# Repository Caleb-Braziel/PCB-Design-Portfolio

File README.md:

# PCB Design Portfolio

This repository contains a curated set of PCB design projects developed for instructional use and technical mentorship. The designs demonstrate practical workflows in schematic capture, hierarchical design, PCB layout, and manufacturability using KiCad and EAGLE.

While many of these projects were created for teaching purposes, they reflect real-world PCB design practices and increasing levels of technical complexity.

---

## Project Overview

The projects in this repository span a range of complexity, from introductory designs to advanced power and embedded systems.

### EAGLE Projects
- **Night Light PCB**  
  A fully fabricated PCB for a night light circuit, including LED and basic power components, laid out and soldered.

### KiCad Projects
- **AC to DC Converter**  
  An AC-DC power supply PCB circuit, designed for voltage conversion and basic power regulation.

- **DC Motor Speed Controller**  
  A PCB for controlling the speed of a DC motor, using discrete components and control circuitry.

- **GPS Tracker with STM32**  
  A microcontroller-based PCB integrating a GPS module for location tracking.

---

## Design Focus

Across these projects, the primary design goals include:
- Clear schematic organization and hierarchy
- Manufacturable PCB layouts
- Proper grounding and power distribution
- Debuggability and clarity for future modification
- Progressive increase in design complexity

---

## Tools & Technologies

- **EDA Tools:** KiCad, EAGLE  
- **Design Skills:** Schematic capture, hierarchical design, PCB layout, ERC/DRC validation  
- **Domains:** Power electronics, motor control, embedded systems  
- **Fabrication:** PCB manufacturing support and hand soldering (select projects)

---

## Notes

Some designs were developed as instructional examples and may not represent finalized commercial products. However, all projects follow industry-standard PCB design practices and are intended to demonstrate technical proficiency and design intent.

---

## Author

Caleb Braziel  
Mechanical Engineering / Embedded & PCB Design

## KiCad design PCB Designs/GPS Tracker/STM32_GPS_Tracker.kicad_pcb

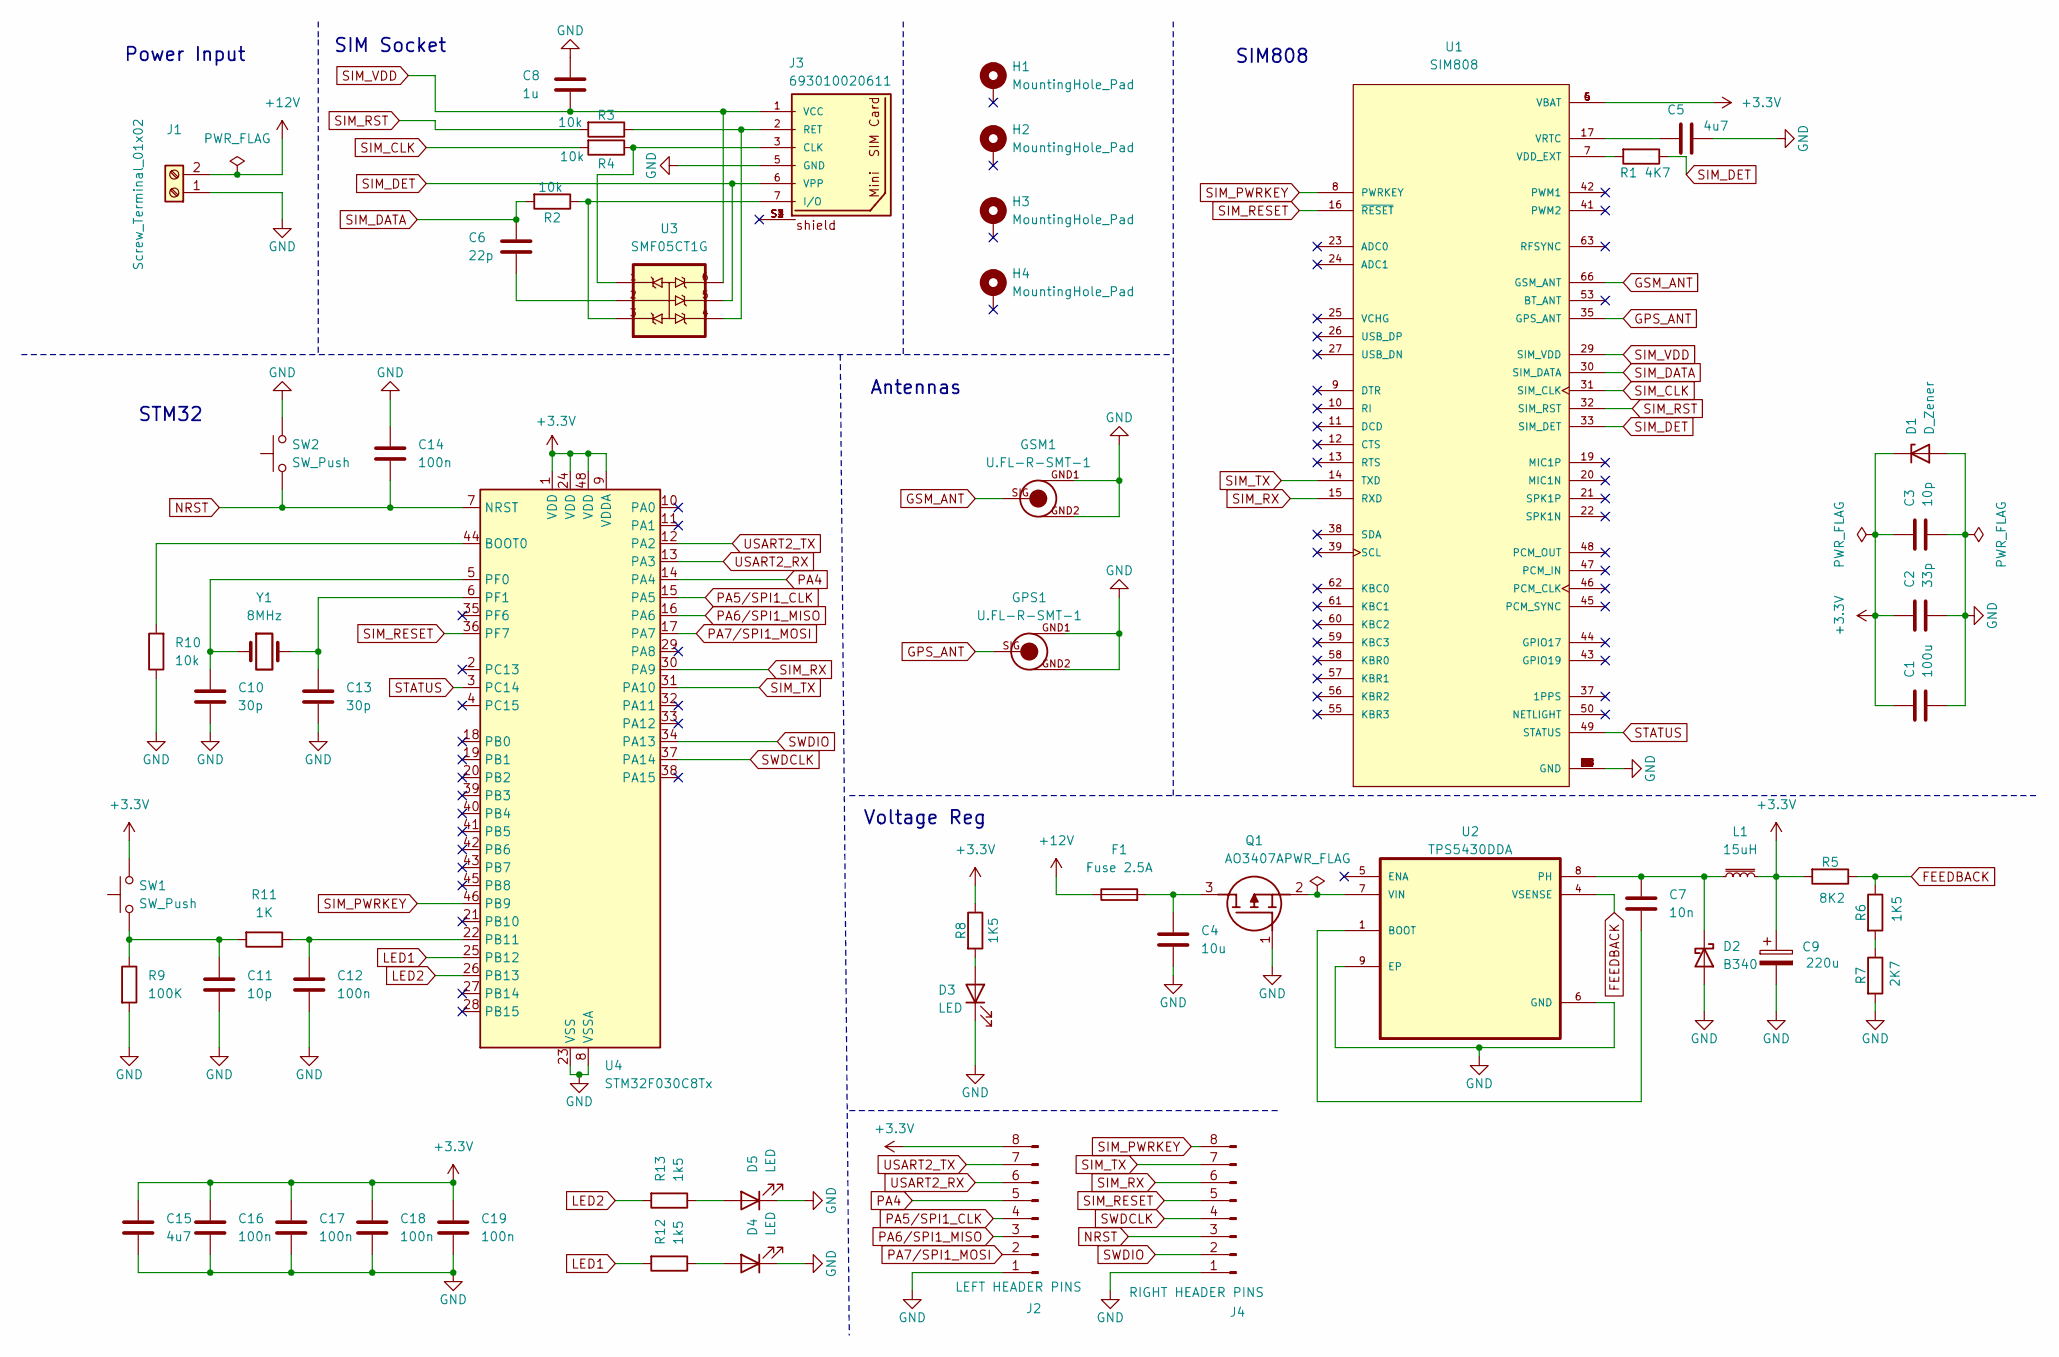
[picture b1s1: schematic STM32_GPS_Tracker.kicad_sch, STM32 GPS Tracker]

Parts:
C1: 100u; C_1206_3216Metric
C2: 33p; C_0402_1005Metric
C3, C11: 10p; C_0402_1005Metric
C4: 10u; C_0805_2012Metric
C5, C15: 4u7; C_0201_0603Metric
C6: 22p; C_0402_1005Metric
C7: 10n; C_0201_0603Metric
C8: 1u; C_0402_1005Metric
C9: 220u; CP_EIA-7343-15_Kemet-W
C10, C13: 30p; C_0402_1005Metric
C12, C14, C16, C17, C18, C19: 100n; C_0402_1005Metric
D1: D_Zener; D_0805_2012Metric
D2: B340; D_SMC
D3, D4, D5: LED; LED_0603_1608Metric
F1: Fuse 2.5A; Fuse_0402_1005Metric
GPS1: U.FL-R-SMT-1
GSM1: U.FL-R-SMT-1
H1, H2, H3, H4: MountingHole_Pad; MountingHole_2.2mm_M2_Pad_Via
J1: Screw_Terminal_01x02; TerminalBlock_Phoenix_MKDS-1,5-2-5.08_1x02_P5.08mm_Horizont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
J2: LEFT HEADER PINS; PinHeader_1x08_P2.54mm_Vertical
J3: 693010020611; PART-NUMBER 693010020611
J4: RIGHT HEADER PINS; PinHeader_1x08_P2.54mm_Vertical
L1: 15uH; L_10.4x10.4_H4.8
Q1: AO3407A; SOT95P280X125-3N; Manufacturer_Part_Number AO3407A
R1: 4K7; R_0402_1005Metric
R2, R3, R4, R10: 10k; R_0402_1005Metric
R5: 8K2; R_0805_2012Metric
R6, R8: 1K5; R_0805_2012Metric
R7: 2K7; R_0805_2012Metric
R9: 100K; R_0201_0603Metric
R11: 1K; R_0603_1608Metric
R12, R13: 1k5; R_0805_2012Metric
SW1, SW2: SW_Push; SW_Push_1P1T_NO_CK_KSC6xxJ
U1: SIM808; XCVR_SIM808; PARTREV 1.03
U2: TPS5430DDA; VREG_LM5017MR_NOPB
U3: SMF05CT1G; SOT65P210X110-6N
U4: STM32F030C8Tx; LQFP-48_7x7mm_P0.5mm
Y1: 8MHz; Crystal_SMD_5032-2Pin_5.0x3.2mm

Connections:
+3.3V: C1.1, C2.1, C3.1, C9.1, C15.1, C16.1, C17.1, C18.1, C19.1, D1.1 (K), J2.8, L1.2, R5.2, R8.1, SW1.2, U1.4 (VBAT), U1.5 (VBAT), U1.6 (VBAT), U4.1 (VDD), U4.9 (VDDA), U4.24 (VDD), U4.48 (VDD)
+12V: F1.1, J1.2
FEEDBACK: R5.1, R6.1, U2.4 (VSENSE)
GND: C1.2, C2.2, C3.2, C4.2, C5.1, C8.1, C9.2, C10.2, C11.2, C12.2, C13.2, C14.1, C15.2, C16.2, C17.2, C18.2, C19.2, D1.2 (A), D2.2 (A), D3.1 (K), D4.1 (K), D5.1 (K), GPS1.GND1, GPS1.GND2, GSM1.GND1, GSM1.GND2, J1.1, J2.1, J3.5 (GND), J4.1, Q1.1 (G), R7.2, R9.2, R10.1, SW2.2, U1.1 (GND), U1.2 (GND), U1.3 (GND), U1.18 (GND), U1.28 (GND), U1.34 (GND), U1.36 (GND), U1.40 (GND), U1.51 (GND), U1.52 (GND), U1.54 (GND), U1.64 (GND), U1.65 (GND), U1.67 (GND), U1.68 (GND), U2.6 (GND), U2.9 (EP), U4.8 (VSSA), U4.23 (VSS), U4.47 (VSS)
GPS_ANT: GPS1.SIG, U1.35 (GPS_ANT)
GSM_ANT: GSM1.SIG, U1.66 (GSM_ANT)
LED1: R12.2, U4.25 (PB12)
LED2: R13.2, U4.26 (PB13)
NRST: C14.2, J4.3, SW2.1, U4.7 (NRST)
unnamed: C6.2, U3.2
unnamed: C11.1, R9.1, R11.2, SW1.1
unnamed: C7.2, D2.1 (K), L1.1, U2.8 (PH)
unnamed: D3.2 (A), R8.2
unnamed: D4.2 (A), R12.1
unnamed: D5.2 (A), R13.1
unnamed: J3.3 (CLK), R4.1, U3.1
unnamed: J3.7 (I/O), R2.1, U3.3
unnamed: J3.2 (RET), R3.1, U3.4
unnamed: C4.1, F1.2, Q1.3 (D)
unnamed: Q1.2 (S), U2.7 (VIN)
unnamed: R6.2, R7.1
unnamed: R1.2, U1.7 (VDD_EXT)
unnamed: C5.2, U1.17 (VRTC)
unnamed: C7.1, U2.1 (BOOT)
unnamed: R10.2, U4.44 (BOOT0)
unnamed: C12.1, R11.1, U4.22 (PB11)
unnamed: C10.1, U4.5 (PF0), Y1.1
unnamed: C13.1, U4.6 (PF1), Y1.2
PA4: J2.5, U4.14 (PA4)
PA5/SPI1_CLK: J2.4, U4.15 (PA5)
PA6/SPI1_MISO: J2.3, U4.16 (PA6)
PA7/SPI1_MOSI: J2.2, U4.17 (PA7)
SIM_CLK: R4.2, U1.31 (SIM_CLK)
SIM_DATA: C6.1, R2.2, U1.30 (SIM_DATA)
SIM_DET: J3.6 (VPP), R1.1, U1.33 (SIM_DET), U3.5
SIM_PWRKEY: J4.8, U1.8 (PWRKEY), U4.46 (PB9)
SIM_RESET: J4.5, U1.16 (~RESET), U4.36 (PF7)
SIM_RST: R3.2, U1.32 (SIM_RST)
SIM_RX: J4.6, U1.15 (RXD), U4.30 (PA9)
SIM_TX: J4.7, U1.14 (TXD), U4.31 (PA10)
SIM_VDD: C8.2, J3.1 (VCC), U1.29 (SIM_VDD), U3.6
STATUS: U1.49 (STATUS), U4.3 (PC14)
SWDCLK: J4.4, U4.37 (PA14)
SWDIO: J4.2, U4.34 (PA13)
USART2_RX: J2.6, U4.13 (PA3)
USART2_TX: J2.7, U4.12 (PA2)

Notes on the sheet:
SIM Socket
SIM808
Power Input
Antennas
STM32
Voltage Reg

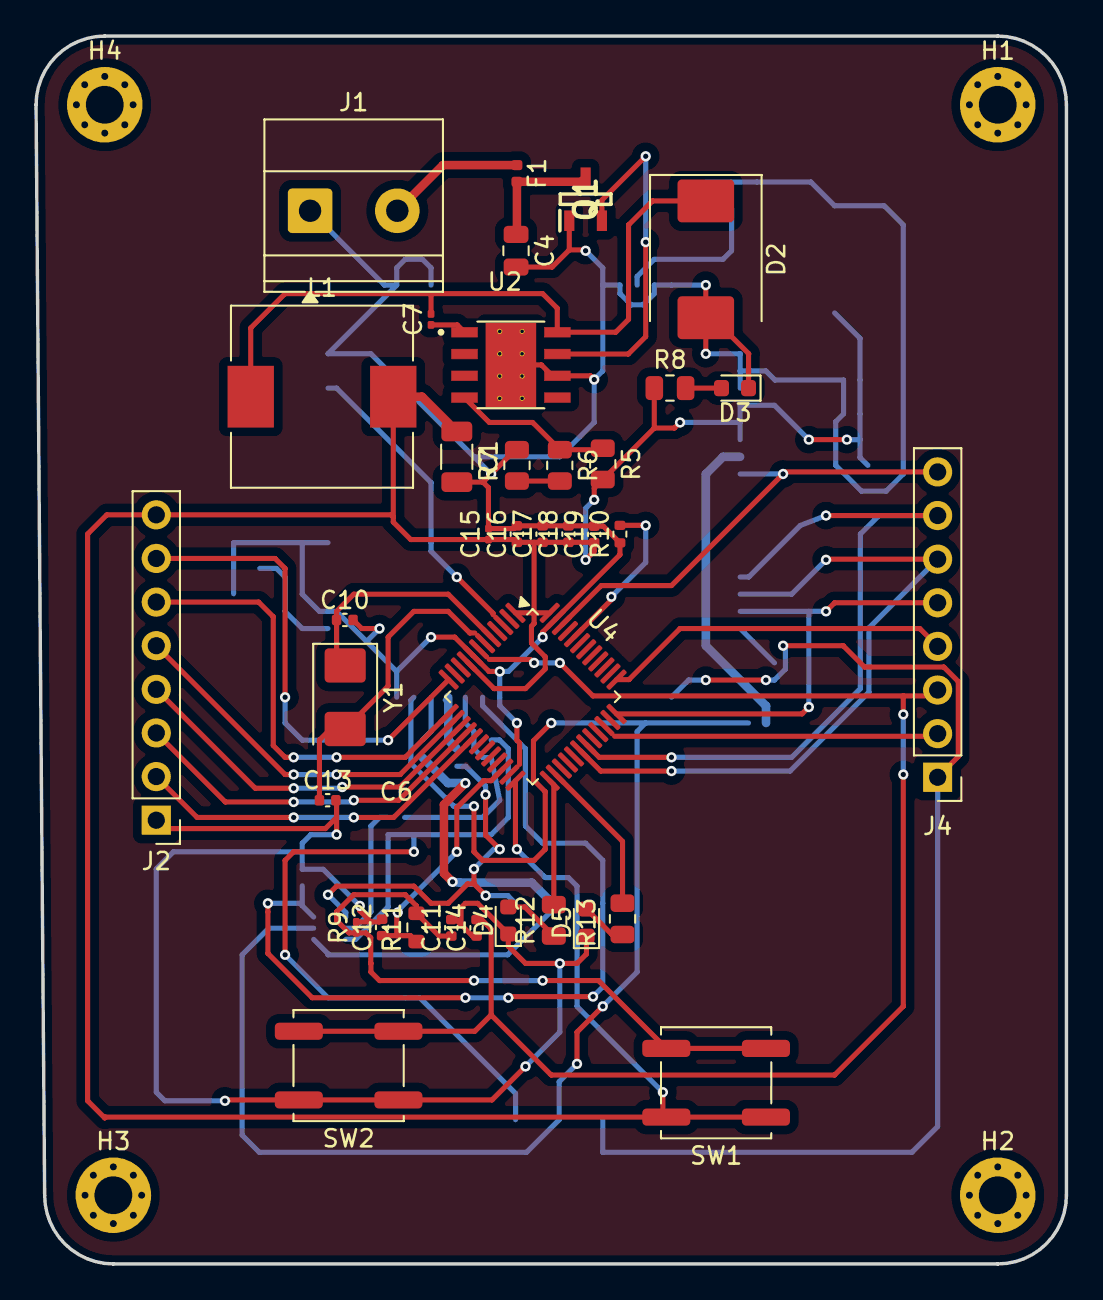
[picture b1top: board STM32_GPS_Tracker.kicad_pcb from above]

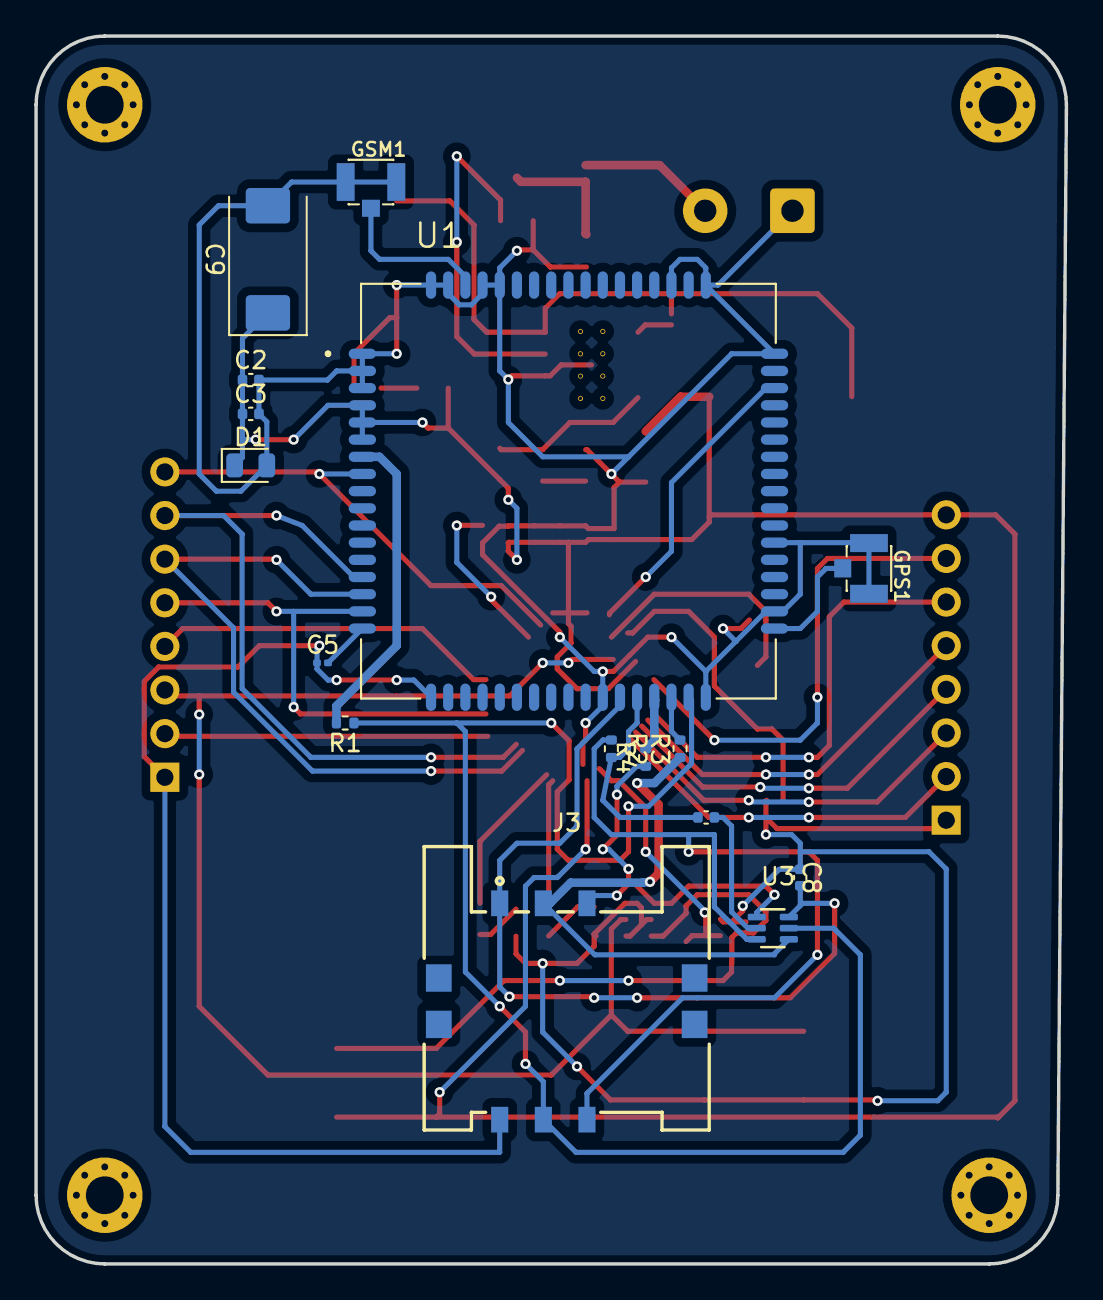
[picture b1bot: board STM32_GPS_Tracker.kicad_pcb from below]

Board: 4 copper layers, 60.0 x 71.5 mm, 57 parts (16 on the bottom side), 46 nets.

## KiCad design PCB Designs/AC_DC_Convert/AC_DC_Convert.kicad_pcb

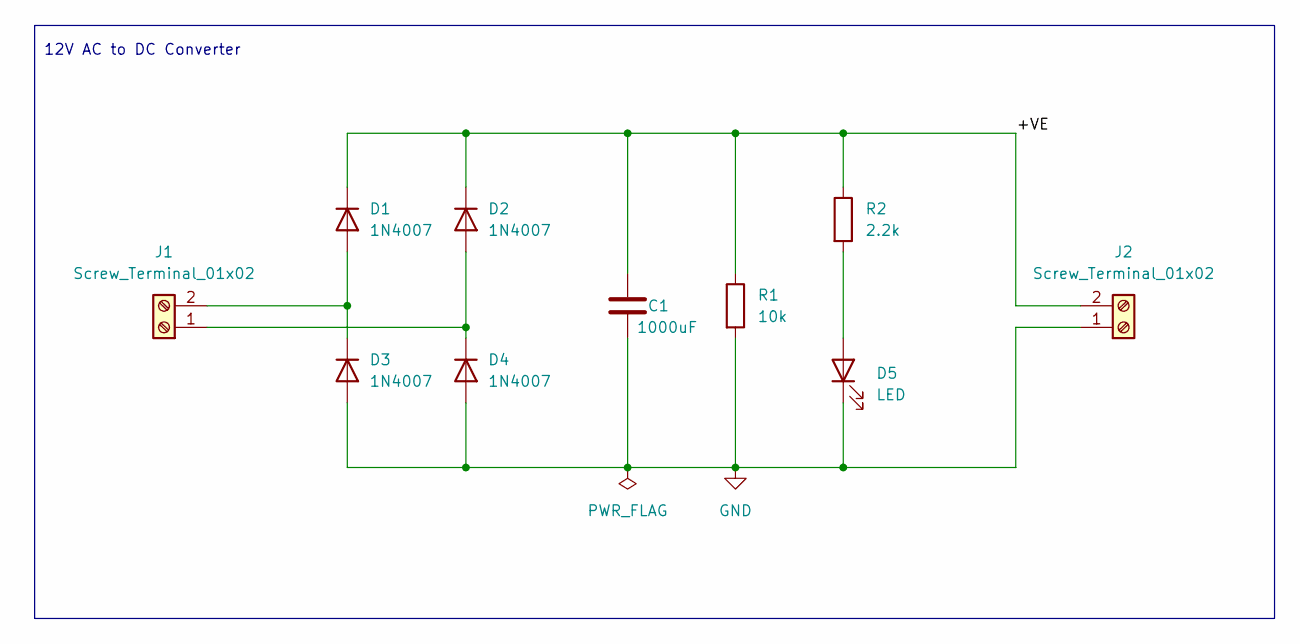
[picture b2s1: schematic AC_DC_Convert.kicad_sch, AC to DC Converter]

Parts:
C1: 1000uF; C_Radial_D8.0mm_H11.5mm_P3.50mm
D1, D2, D3, D4: 1N4007; D_DO-41_SOD81_P10.16mm_Horizontal
D5: LED; LED_D5.0mm
J1, J2: Screw_Terminal_01x02; TerminalBlock_Phoenix_MKDS-1,5-2-5.08_1x02_P5.08mm_Horizont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
R1: 10k; R_Axial_DIN0204_L3.6mm_D1.6mm_P7.62mm_Horizontal
R2: 2.2k; R_Axial_DIN0204_L3.6mm_D1.6mm_P7.62mm_Horizontal

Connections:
/+VE: C1.1, D1.1 (K), D2.1 (K), J2.2, R1.1, R2.1
GND: C1.2, D3.2 (A), D4.2 (A), D5.1 (K), J2.1, R1.2
unnamed: D1.2 (A), D3.1 (K), J1.2
unnamed: D2.2 (A), D4.1 (K), J1.1
unnamed: D5.2 (A), R2.2

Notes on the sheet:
12V AC to DC Converter

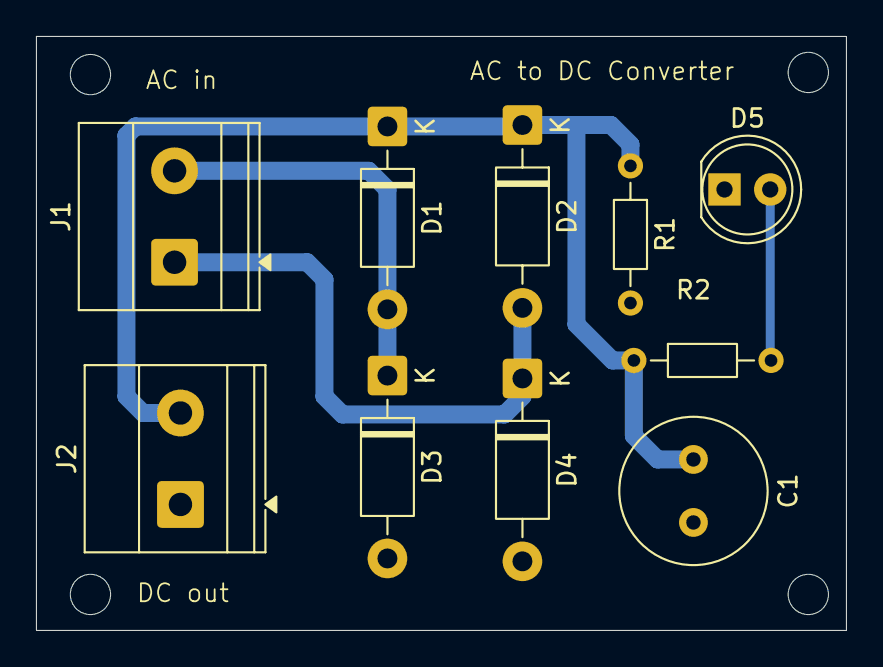
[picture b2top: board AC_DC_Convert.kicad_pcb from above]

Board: 2 copper layers, 45.0 x 33.0 mm, 10 parts (0 on the bottom side), 5 nets.

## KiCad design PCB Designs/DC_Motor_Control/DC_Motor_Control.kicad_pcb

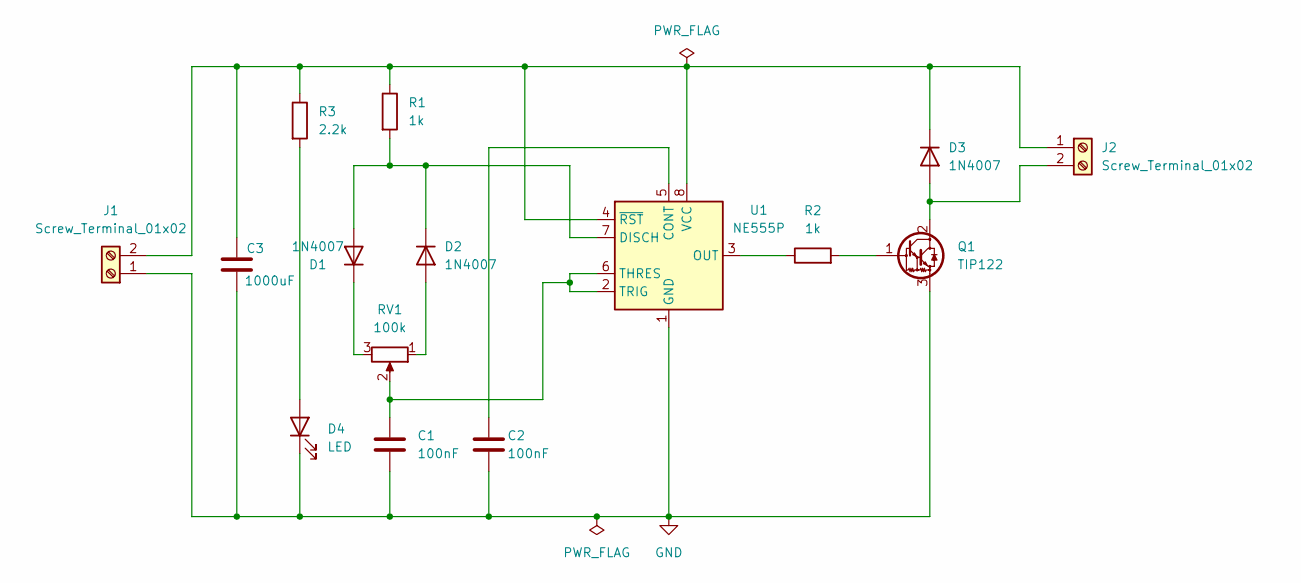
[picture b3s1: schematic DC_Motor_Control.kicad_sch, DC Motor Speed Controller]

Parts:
C1, C2: 100nF; C_Disc_D4.7mm_W2.5mm_P5.00mm
C3: 1000uF; CP_Radial_D10.0mm_P5.00mm
D1, D2, D3: 1N4007; D_DO-41_SOD81_P10.16mm_Horizontal
D4: LED; LED_D5.0mm
J1, J2: Screw_Terminal_01x02; TerminalBlock_Phoenix_MKDS-1,5-2-5.08_1x02_P5.08mm_Horizont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
Q1: TIP122; TO-220-3_Vertical
R1, R2: 1k; R_Axial_DIN0204_L3.6mm_D1.6mm_P7.62mm_Horizontal
R3: 2.2k; R_Axial_DIN0204_L3.6mm_D1.6mm_P7.62mm_Horizontal
RV1: 100k; Potentiometer_Alps_RK163_Single_Horizontal
U1: NE555P; DIP-8_W7.62mm

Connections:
GND: C1.2, C2.2, C3.2, D4.1 (K), J1.1, Q1.3 (E), U1.1 (GND)
unnamed: D1.2 (A), D2.1 (K), R1.2, U1.7 (DISCH)
unnamed: D1.1 (K), RV1.3
unnamed: D2.2 (A), RV1.1
unnamed: D3.2 (A), J2.2, Q1.2 (C)
unnamed: C3.1, D3.1 (K), J1.2, J2.1, R1.1, R3.1, U1.4 (~RST), U1.8 (VCC)
unnamed: D4.2 (A), R3.2
unnamed: Q1.1 (B), R2.2
unnamed: C2.1, U1.5 (CONT)
unnamed: R2.1, U1.3 (OUT)
unnamed: C1.1, RV1.2, U1.2 (TRIG), U1.6 (THRES)

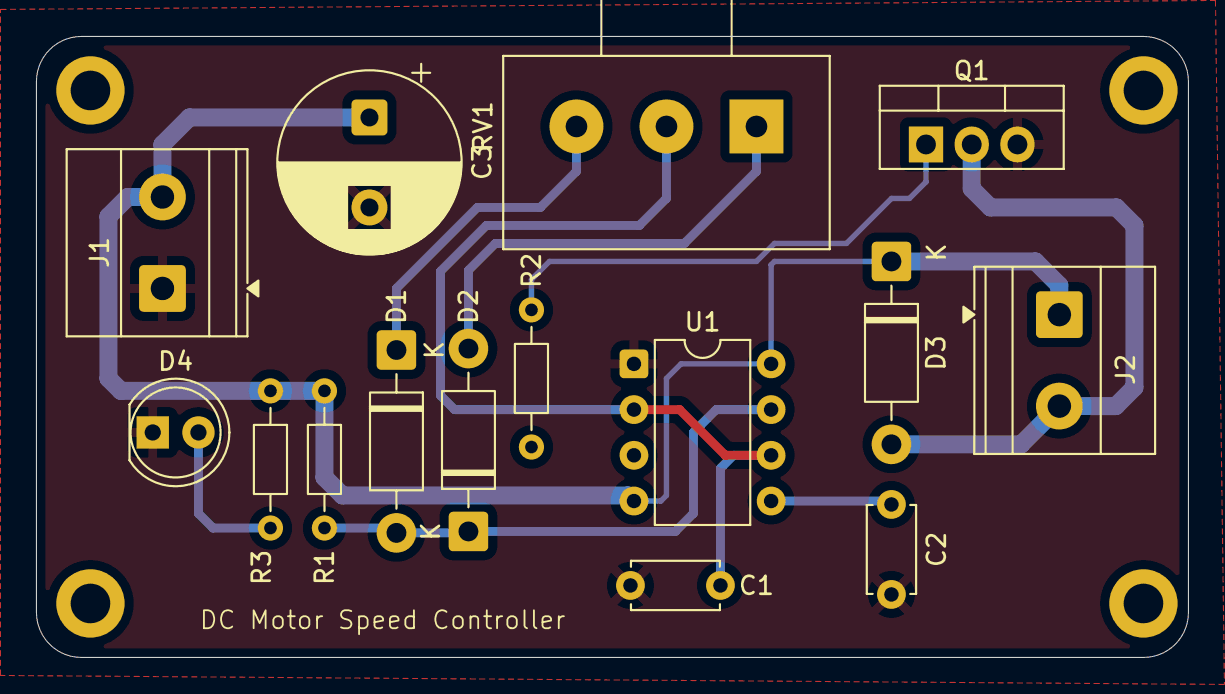
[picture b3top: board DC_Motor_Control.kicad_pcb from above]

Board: 2 copper layers, 64.0 x 34.5 mm, 15 parts (0 on the bottom side), 11 nets.
